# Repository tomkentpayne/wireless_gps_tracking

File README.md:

wireless_gps_tracking
=====================

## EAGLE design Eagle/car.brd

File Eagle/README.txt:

Order number: 100021590

Note:
  Layers: 2
  Silk screen: top and bottom
  Soldermask: top and bottom
  File "car.GML" is the board outline
  Drill format: Excellon, 2.4 precision.

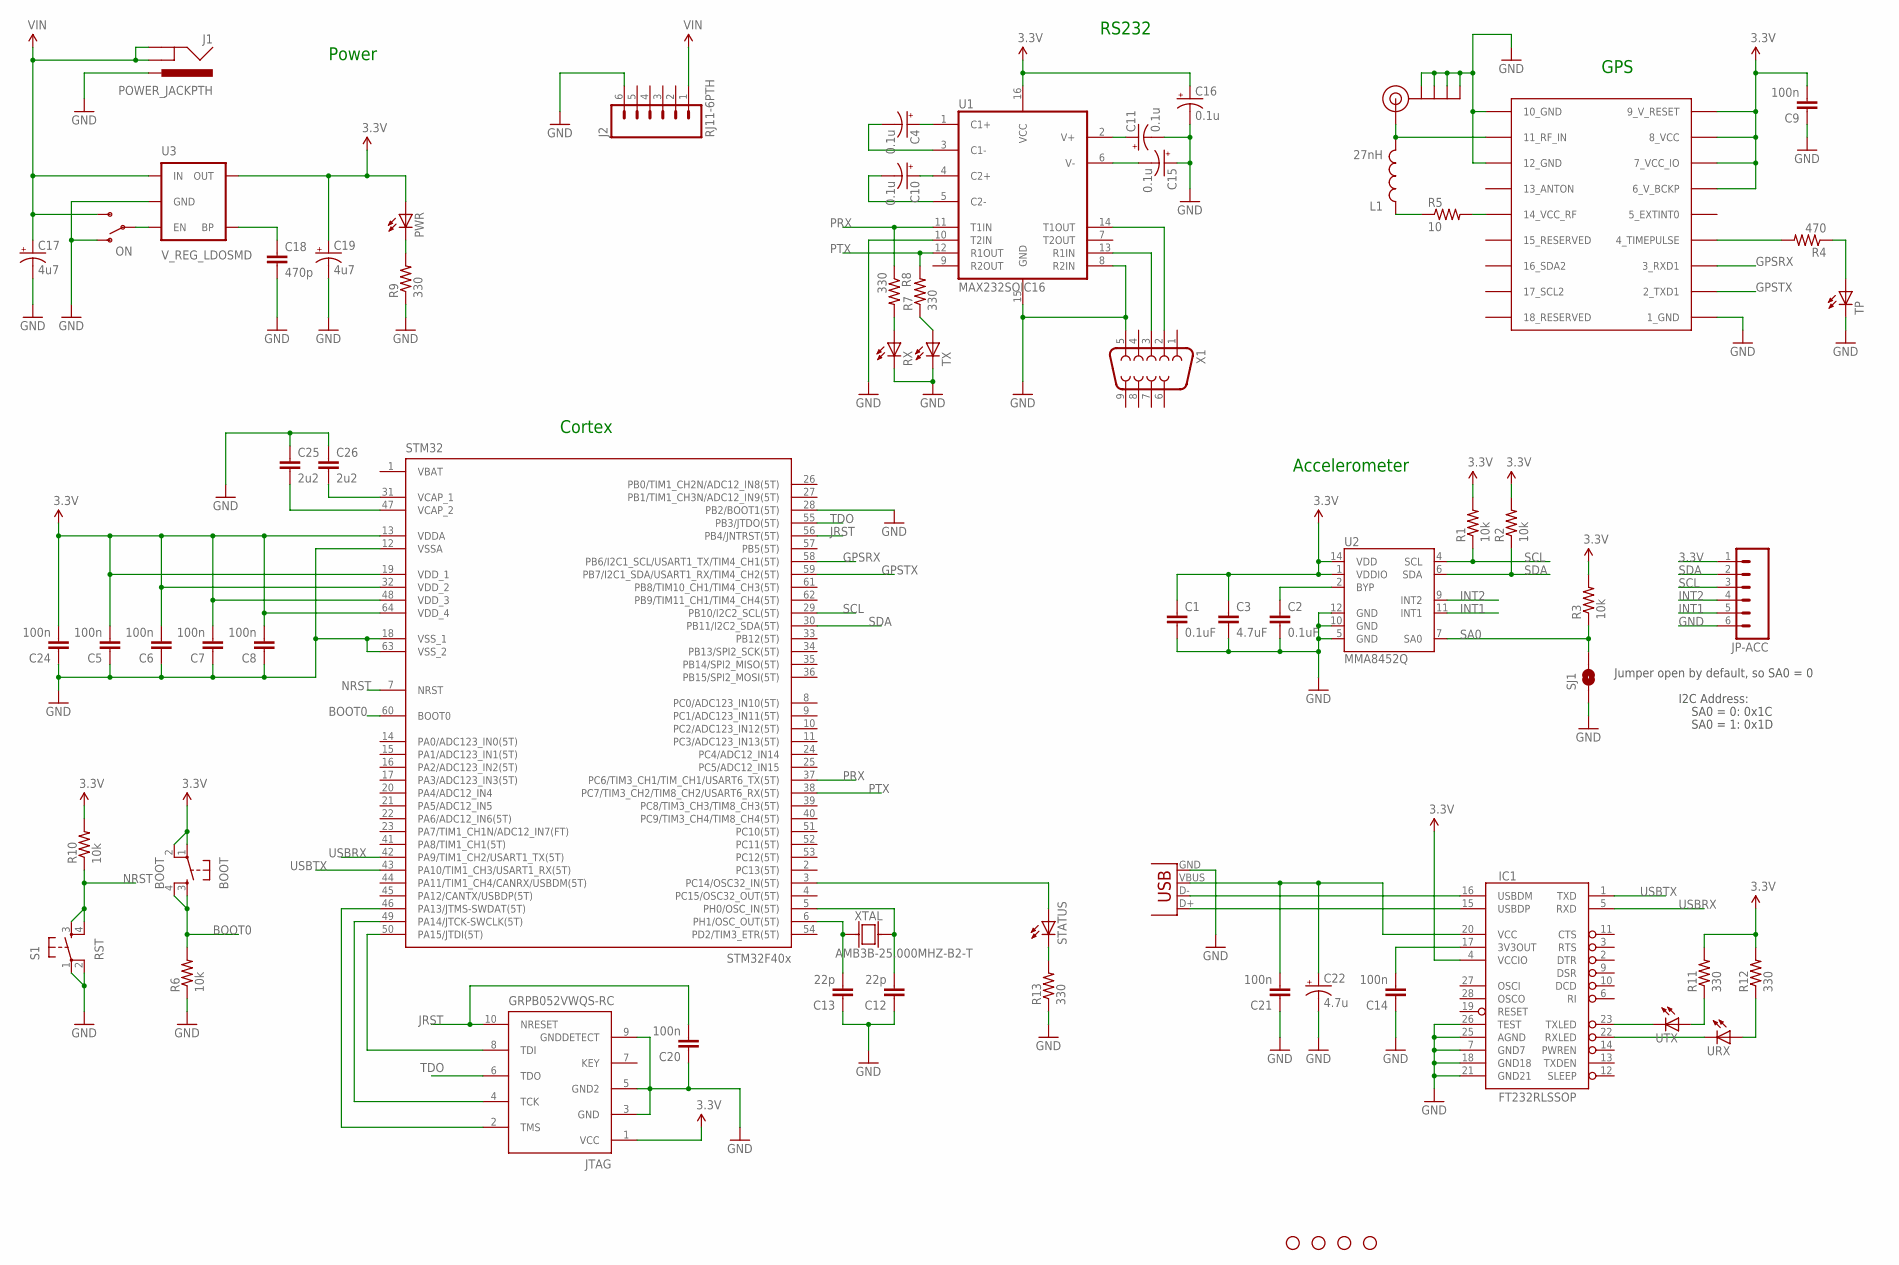
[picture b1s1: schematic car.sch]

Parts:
BOOT: BOOT; TACTILE_SWITCH_SMD
C1, C2: 0.1uF; 0603-CAP
C3: 4.7uF; 0603-CAP
C4, C10, C11, C15, C16: 0.1u; EIA3216
C5, C6, C7, C8, C9, C14, C20, C21, C24: 100n; 0603-CAP
C12, C13: 22p; 0603-CAP
C17, C19: 4u7; EIA3216
C18: 470p; 0603-CAP
C22: 4.7u; EIA3216
C25, C26: 2u2; 0603-CAP
IC1: FT232RLSSOP; SSOP28DB
J1: POWER_JACKPTH; POWER_JACK_PTH
J2: RJ11-6PTH; RJ11-6
J$1: SMA_EDGE; SMA-EDGE
JP1, JP2, JP3, JP4: STAND-OFF
JP-ACC: M06SIP; 1X06
JTAG: GRPB052VWQS-RC; DEBUG
L1: 27nH; 0603
ON: SWITCH-SPDTPTH; SWITCH-SPDT
PWR: LED0603; LED-0603
R1, R2, R3, R6, R10: 10k; 0603-RES
R4: 470; 0603-RES
R5: 10; 0603-RES
R7, R8, R9, R11, R12, R13: 330; 0603-RES
RX: LED0603; LED-0603
S1: RST; TACTILE_SWITCH_SMD
SJ1: SOLDERJUMPERNO; SJ_2S-NO
STATUS: LED0603; LED-0603
STM32: STM32F405R; TQFP64
TP: LED0603; LED-0603
TX: LED0603; LED-0603
U1: MAX232SOIC16; SO016
U2: MMA8452Q; QFN-16_0.5MM
U3: V_REG_LDOSMD; SOT23-5
U$1: UBLOX_MAX-6
URX: LED0603; LED-0603
USB: USB-SMD-NS; USB-MINIB-NOSTOP
UTX: LED0603; LED-0603
X1: DB9FEMALE; DB9
XTAL: AMB3B-25.000MHZ-B2-T; 4LCC

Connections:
3.3V: BOOT.1, BOOT.2, C1.1, C3.1, C5.2, C6.2, C7.2, C8.2, C9.2, C16.A (+), C19.A (+), C24.2, IC1.4 (VCCIO), JP-ACC.1, JTAG.1 (VCC), PWR.A, R1.2, R2.2, R3.2, R10.2, R11.2, R12.2, STM32.13 (VDDA), STM32.19 (VDD_1), STM32.32 (VDD_2), STM32.48 (VDD_3), STM32.64 (VDD_4), U1.16 (VCC), U2.1 (VDDIO), U2.14 (VDD), U3.5 (OUT), U$1.6_V_BCKP, U$1.7_VCC_IO, U$1.8_VCC, U$1.9_V_RESET
3.3V1: STATUS.A, STM32.3 (PC14/OSC32_IN(5T))
BOOT0: BOOT.3, BOOT.4, R6.2, STM32.60 (BOOT0)
BYP: C2.1, U2.2 (BYP)
GND: C1.2, C2.2, C3.2, C5.1, C6.1, C7.1, C8.1, C9.1, C11.C (-), C12.1, C13.1, C14.1, C15.A (+), C16.C (-), C17.C (-), C18.2, C19.C (-), C20.1, C21.1, C22.C (-), C24.1, C25.1, C26.1, IC1.7 (GND7), IC1.18 (GND18), IC1.21 (GND21), IC1.25 (AGND), IC1.26 (TEST), J1.PWR, J2.6, J$1.GND@0 (GND), J$1.GND@1 (GND), J$1.GND@2 (GND), J$1.GND@3 (GND), JP-ACC.6, JTAG.3 (GND), JTAG.5 (GND2), JTAG.9 (GNDDETECT), ON.1 (O), R6.1, R9.1, R13.1, RX.C, S1.1, S1.2, SJ1.1, STM32.12 (VSSA), STM32.18 (VSS_1), STM32.28 (PB2/BOOT1(5T)), STM32.63 (VSS_2), TP.C, TX.C, U1.8 (R2IN), U1.10 (T2IN), U1.15 (GND), U2.5 (GND), U2.10 (GND), U2.12 (GND), U3.2 (GND), U$1.1_GND, U$1.10_GND, U$1.12_GND, USB.GND, X1.5
GPSRX: STM32.58 (PB6/I2C1_SCL/USART1_TX/TIM4_CH1(5T)), U$1.3_RXD1
GPSTX: STM32.59 (PB7/I2C1_SDA/USART1_RX/TIM4_CH2(5T)), U$1.2_TXD1
INT1: JP-ACC.5, U2.11 (INT1)
INT2: JP-ACC.4, U2.9 (INT2)
JRST: C20.2, JTAG.10 (NRESET), STM32.56 (PB4/JNTRST(5T))
unnamed: U1.14 (T1OUT), X1.2
unnamed: R4.1, TP.A
unnamed: R4.2, U$1.4_TIMEPULSE
unnamed: C15.C (-), U1.6 (V-)
unnamed: L1.1, R5.1
unnamed: R5.2, U$1.14_VCC_RF
unnamed: J$1.SIG (SIGNAL), L1.2, U$1.11_RF_IN
unnamed: C12.2, STM32.5 (PH0/OSC_IN(5T)), XTAL.3
unnamed: PWR.C, R9.2
unnamed: C11.A (+), U1.2 (V+)
unnamed: C4.A (+), U1.1 (C1+)
unnamed: C4.C (-), U1.3 (C1-)
unnamed: C10.A (+), U1.4 (C2+)
unnamed: C10.C (-), U1.5 (C2-)
unnamed: U1.13 (R1IN), X1.3
unnamed: R7.1, TX.A
unnamed: R8.2, RX.A
unnamed: C13.2, STM32.6 (PH1/OSC_OUT(5T)), XTAL.1
unnamed: C18.1, U3.4 (BP)
unnamed: R13.2, STATUS.C
unnamed: C26.2, STM32.31 (VCAP_1)
unnamed: ON.2, U3.3 (EN)
unnamed: IC1.16 (USBDM), USB.D-
unnamed: IC1.15 (USBDP), USB.D+
unnamed: C21.2, C22.A (+), IC1.20 (VCC), USB.VBUS
unnamed: IC1.23 (TXLED), UTX.C
unnamed: IC1.22 (RXLED), URX.C
unnamed: R11.1, UTX.A
unnamed: R12.1, URX.A
unnamed: C25.2, STM32.47 (VCAP_2)
unnamed: C14.2, IC1.17 (3V3OUT)
NRST: R10.1, S1.3, S1.4, STM32.7 (NRST)
PRX: R8.1, STM32.37 (PC6/TIM3_CH1/TIM_CH1/USART6_TX(5T)), U1.11 (T1IN)
PTX: R7.2, STM32.38 (PC7/TIM3_CH2/TIM8_CH2/USART6_RX(5T)), U1.12 (R1OUT)
SA0: R3.1, SJ1.2, U2.7 (SA0)
SCL: JP-ACC.3, R1.1, STM32.29 (PB10/I2C2_SCL(5T)), U2.4 (SCL)
SDA: JP-ACC.2, R2.1, STM32.30 (PB11/I2C2_SDA(5T)), U2.6 (SDA)
TCK: JTAG.4 (TCK), STM32.49 (PA14/JTCK-SWCLK(5T))
TDI: JTAG.8 (TDI), STM32.50 (PA15/JTDI(5T))
TDO: JTAG.6 (TDO), STM32.55 (PB3/JTDO(5T))
TMS: JTAG.2 (TMS), STM32.46 (PA13/JTMS-SWDAT(5T))
USBRX: IC1.5 (RXD), STM32.42 (PA9/TIM1_CH2/USART1_TX(5T))
USBTX: IC1.1 (TXD), STM32.43 (PA10/TIM1_CH3/USART1_RX(5T))
VIN: C17.A (+), J1.GND, J1.GNDBREAK, J2.1, ON.3 (S), U3.1 (IN)

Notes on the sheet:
I2C Address:
SA0 = 0: 0x1C
SA0 = 1: 0x1D
Jumper open by default, so SA0 = 0
Accelerometer
Power
GPS
RS232
Cortex

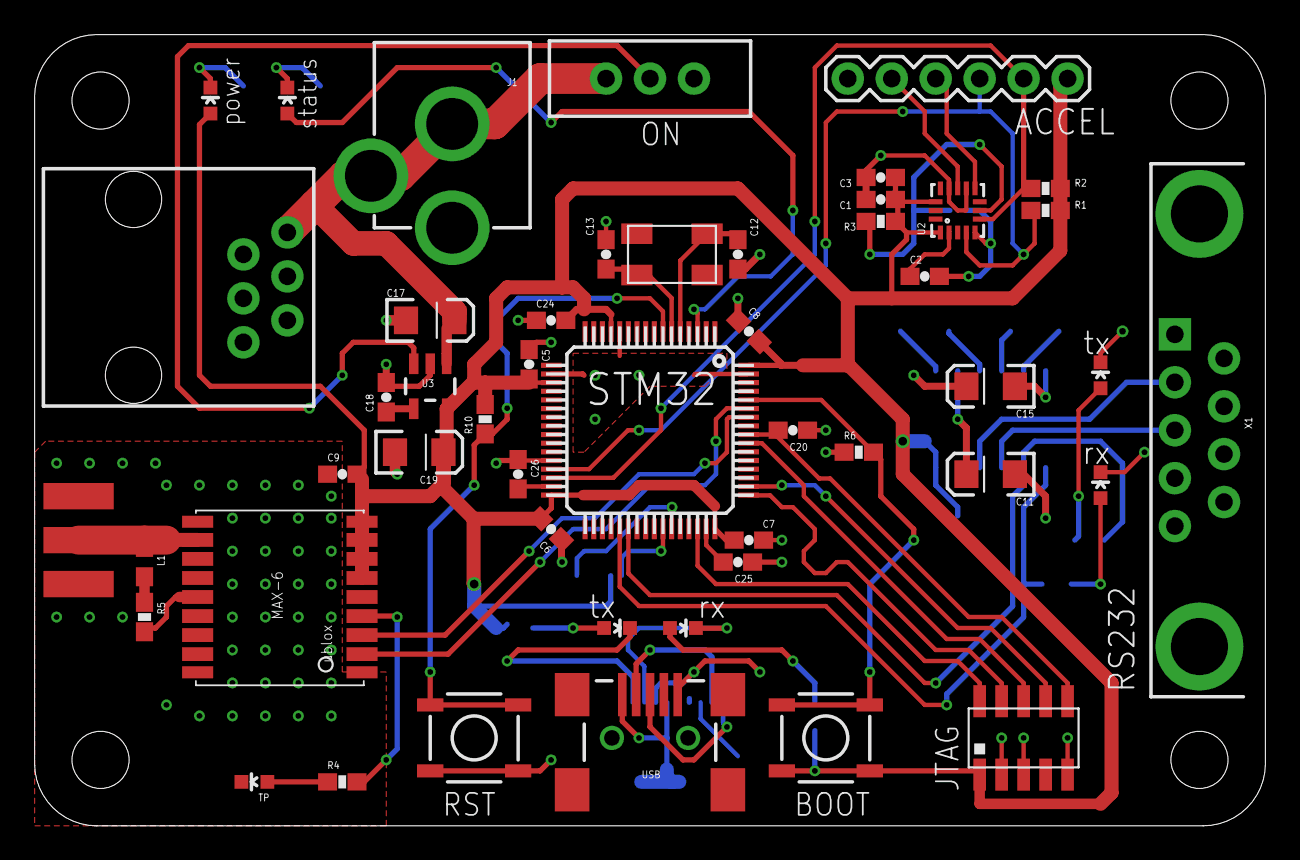
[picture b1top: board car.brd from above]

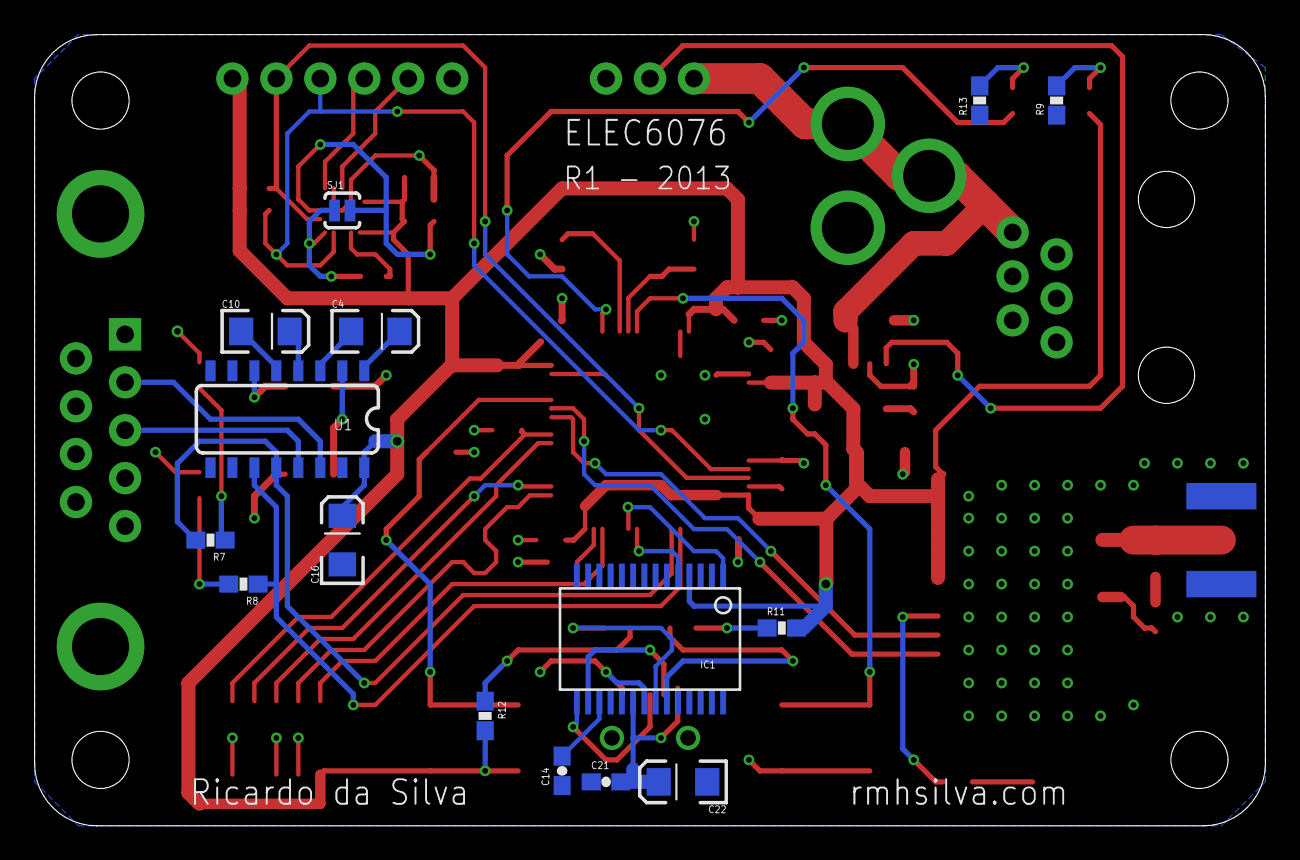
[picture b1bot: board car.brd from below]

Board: 2 copper layers, 71.1 x 45.7 mm, 68 parts (15 on the bottom side), 54 nets.

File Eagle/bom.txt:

Partlist exported from /Users/ric/Documents/eagle/my_projects/elec6067/car.sch at 15/12/2013 19:17

Qty Value                Device               Package            Parts                                  Description                                     
1                        DB9FEMALE            DB9                X1                                     DB9 Connector                                   
7                        LED0603              LED-0603           PWR, RX, STATUS, TP, TX, URX, UTX      LEDs                                            
1                        M06SIP               1X06               JP-ACC                                 Header 6                                        
1                        SOLDERJUMPERNO       SJ_2S-NO           SJ1                                    Solder Jumper                                   
1                        SWITCH-SPDTPTH       SWITCH-SPDT        ON                                     SPST Switch                                     
5   0.1u                 CAP_POL1206          EIA3216            C4, C10, C11, C15, C16                 Capacitor Polarized                             
1   10                   RESISTOR0603-RES     0603-RES           R5                                     Resistor                                        
9   100n                 CAP0603-CAP          0603-CAP           C5, C6, C7, C8, C9, C14, C20, C21, C24 Capacitor                                       
2   10k                  RESISTOR0603-RES     0603-RES           R1, R2, R3, R6, R10                    Resistor                                        
2   22p                  CAP0603-CAP          0603-CAP           C12, C13                               Capacitor                                       
1   27nH                 INDUCTOR0603         0603               L1                                     Inductors                                       
2   2u2                  CAP0603-CAP          0603-CAP           C25, C26                               Capacitor                                       
6   330                  RESISTOR0603-RES     0603-RES           R7, R8, R9, R11, R12, R13              Resistor                                        
1   4.7u                 CAP_POL1206          EIA3216            C22                                    Capacitor Polarized                             
1   470                  RESISTOR0603-RES     0603-RES           R4                                     Resistor                                        
1   470p                 CAP0603-CAP          0603-CAP           C18                                    Capacitor                                       
2   4u7                  CAP_POL1206          EIA3216            C17, C19                               Capacitor Polarized                             
1   AMB3B-25.000MHZ-B2-T AMB3B-25.000MHZ-B2-T 4LCC               XTAL                                   CRYSTAL, 25.000MHZ 18PF SMD                     
1   BOOT                 TAC_SWITCHSMD        TACTILE_SWITCH_SMD BOOT                                   Momentary Switch                                
1   FT232RLSSOP          FT232RLSSOP          SSOP28DB           IC1                                    USB UART                                        
1   GRPB052VWQS-RC       GRPB052VWQS-RC       DEBUG              JTAG                                   CONN HEADER 0.050" 10PS DL SMD AU               
1   MAX232SOIC16         MAX232SOIC16         SO016              U1                                     RS232 Transceiver
1   POWER_JACKPTH        POWER_JACKPTH        POWER_JACK_PTH     J1                                     Power Jack                                      
1   RJ11-6PTH            RJ11-6PTH            RJ11-6             J2                                     RJ11 Jack                                       
1   RST                  TAC_SWITCHSMD        TACTILE_SWITCH_SMD S1                                     Momentary Switch                                
1   SMA_EDGE             SMA_EDGE             SMA-EDGE           J$1                                    SMA Antenna Connector                           
4   STAND-OFF            STAND-OFF            STAND-OFF          JP1, JP2, JP3, JP4                     #4 Stand Off                                    
1   STM32F405R           STM32F405R           TQFP64             STM32                                  STM32F405 64 pin LQFP                           
1   UBLOX_MAX-6          UBLOX_MAX-6          UBLOX_MAX-6        U$1                                    UBLOX MAX-6                                     
1   USB-SMD-NS           USB-SMD-NS           USB-MINIB-NOSTOP   USB                                    USB Connectors                                  
1   V_REG_LDOSMD         V_REG_LDOSMD         SOT23-5            U3                                     Voltage Regulator LDO

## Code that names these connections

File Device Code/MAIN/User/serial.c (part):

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
/*
* PINS
* GPS: USART1 PB6 Tx, PB7 Rx
* USB: USART1 PA9 Tx, PA10 Rx
*/

#define MESSAGE_NO_FIX "$GPGLL,,,,,104439.00,V,N*"
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
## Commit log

2013-12-06 gitignore
2013-12-06 Complete stm32 code folder
    Ready to go
2013-12-23 Added Eagle design files and Gerbers
2014-01-11 More files/structure
2014-01-11 USB Serial, globals file, main structure + help
2014-01-12 GPS nmea parsing
2014-01-12 GPS data receive handler
    Rx pin still currently set to USB not GPS
2014-01-12 today's messing
2014-01-12 bin file
2014-01-13 little fix
2014-01-13 GPIO testing structure + project
2014-01-13 UART tessting structure + project
    also gpio testing fix and MAIN project file update (assuming no one's
    touched so is ok)
2014-01-13 Update Xtal to 8MHz
2014-01-14 Serial update for testing
2014-01-15 Simple blinky code that works :)
2014-01-15 Xtal code update in MAIN, should work now
2014-01-15 Todays stuff (timer, gpio)
2014-01-18 Updates. rs232 not sure. nmea parsing in place
2014-01-19 WOOOOO!!!
2014-01-19 Yeah boi
2014-01-19 LED flashes when no gps fix, else on
2014-01-26 Server thangs
2014-01-26 These were our final changes

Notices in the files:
parts and their libraries:
SparkFun-Passives: Licensing: CC v3.0 Share-Alike You are welcome to use this library for commercial purposes.
